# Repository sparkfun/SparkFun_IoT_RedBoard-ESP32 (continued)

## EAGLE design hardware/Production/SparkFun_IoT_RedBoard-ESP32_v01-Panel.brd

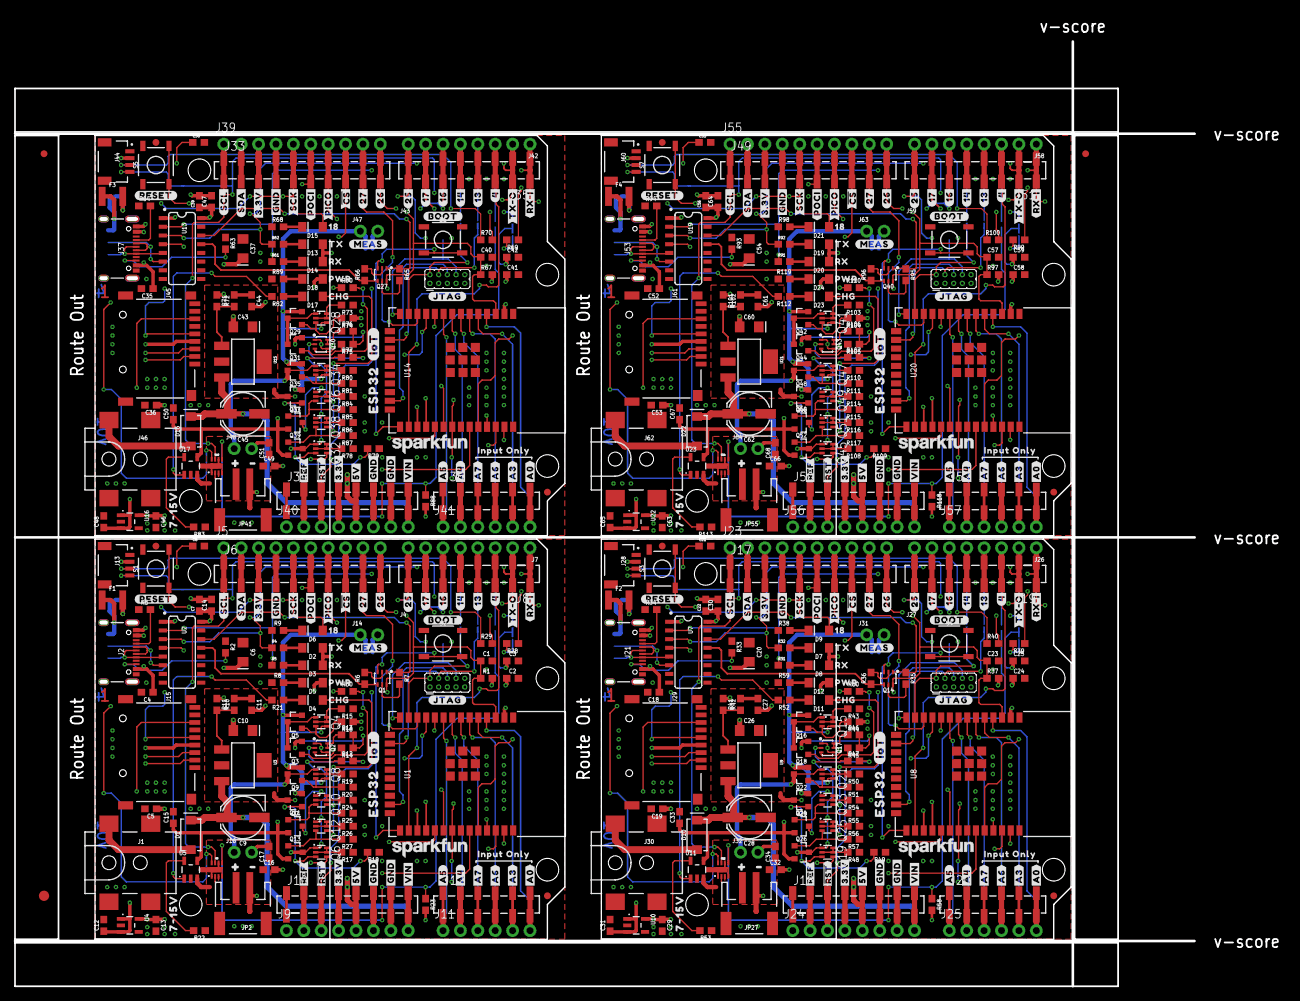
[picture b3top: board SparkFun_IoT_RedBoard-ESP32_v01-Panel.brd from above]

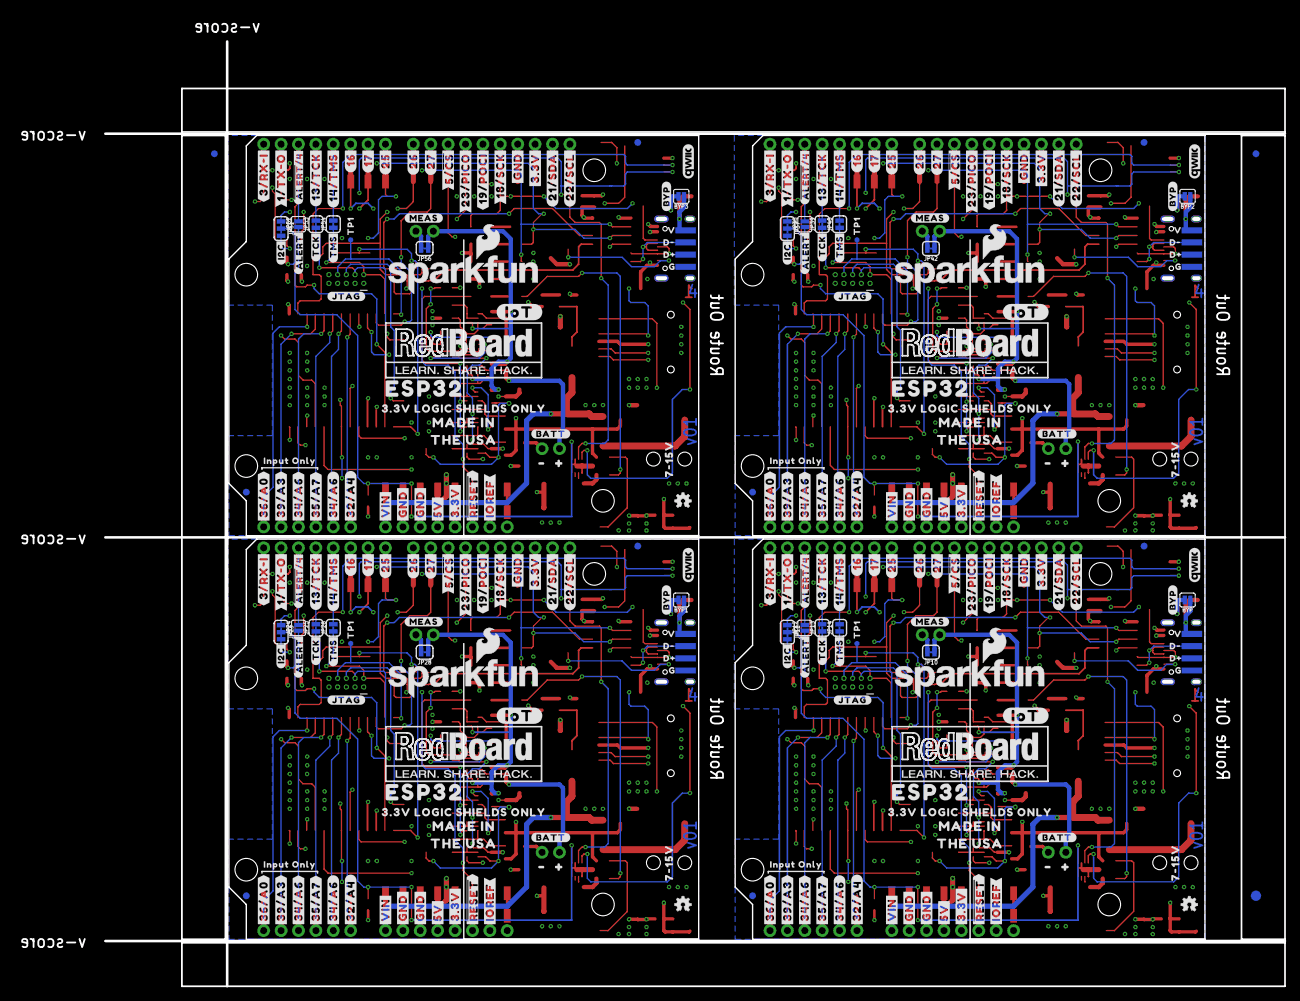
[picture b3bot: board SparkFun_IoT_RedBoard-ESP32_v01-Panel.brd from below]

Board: 4 copper layers, 172.2 x 137.9 mm, 850 parts (271 on the bottom side), 296 nets.

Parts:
BYP, BYP1, BYP2, BYP3: JUMPER-SMT_2_NO_SILK; SMT-JUMPER_2_NO_SILK
C1, C2, C4, C5, C7, C11, C12, C13, C17, C18, C19, C22, C23, C24, C27, C29, C31, C34, C35, C36, C39, C40, C41, C44, C46, C48, C51, C52, C53, C56, C57, C58, C61, C63, C65, C68: 0.1uF; 0603
C3, C14, C25, C30, C42, C47, C59, C64: 10uF; 0603
C6, C10, C20, C26, C37, C43, C54, C60: 10uF; EIA3216
C8, C21, C38, C55: 10nF; 0603
C9, C28, C45, C62: 47uF; PANASONIC_D
C15, C16, C32, C33, C49, C50, C66, C67: 4.7uF; 0603
D1, D10, D16, D22: 1A/40V/500mV; SMA-DIODE
D2, D7, D13, D19: GREEN; LED-1206-HIDDENSILK
D3, D8, D14, D20: YELLOW; LED-1206-HIDDENSILK
D4, D11, D17, D23: RED; LED-1206-HIDDENSILK
D5, D12, D18, D24: PWR; LED-1206-HIDDENSILK
D6, D9, D15, D21: BLUE; LED-1206-HIDDENSILK
E$1, E$2, E$3, E$4: FIDUCIAL-1X2
E$5, E$6: FIDUCIAL-1.5X3
F1, F2, F3, F4: 6V/2A; 1210
J1, J30, J46, J62: 5.5x2.1mm Barrel; POWER_JACK_SMD
J2, J21, J37, J53: USB C; USB-C-16P-2LAYER-PADS
J3, J22, J38, J54: USB_SOLDER_PADS; USB-SOLDER-PADS
J4, J27, J43, J59: 2X5_PTH_SILK_.05
J5, J23, J39, J55: M10NO_SILK; 1X10_NO_SILK
J6, J17, J33, J49: 1X10_SMD_COMBINED
J7, J9, J24, J26, J40, J42, J56, J58: 1X08_NO_SILK
J8, J10, J18, J19, J34, J35, J50, J51: 1X08_SMD_COMBINED
J11, J25, J41, J57: 1X06_NO_SILK
J12, J20, J36, J52: 1X06_SMD_STRAIGHT_COMBO
J13, J28, J44, J60: QWIIC_RIGHT_ANGLE; JST04_1MM_RA
J14, J16, J31, J32, J47, J48, J63, J64: 1X02_NO_SILK
J15, J29, J45, J61: MICRO-SD-PUSH-PUSH-EXT-PIN; MICROSD-EXTERNALPIN
JP1, JP7, JP8, JP9, JP19, JP20, JP21, JP22, JP33, JP34, JP35, JP36, JP47, JP48, JP49, JP50: FIDUCIAL1X2; FIDUCIAL-1X2
JP2, JP27, JP41, JP55: LiPo; JST-2-SMD
JP3, JP4, JP5, JP6, JP15, JP16, JP17, JP18, JP29, JP30, JP31, JP32, JP43, JP44, JP45, JP46: STAND-OFF
JP10, JP13, JP14, JP25, JP26, JP28, JP39, JP40, JP42, JP53, JP54, JP56: JUMPER-SMT_2_NC_TRACE_SILK; SMT-JUMPER_2_NC_TRACE_SILK
JP11, JP23, JP37, JP51: JUMPER-SMT_3_2-NC_TRACE_SILK; SMT-JUMPER_3_2-NC_TRACE_SILK
JP12, JP24, JP38, JP52: JUMPER-SMT_2_NO_SILK; SMT-JUMPER_2_NO_SILK
LOGO1, LOGO4, LOGO9, LOGO13: SFE_LOGO_NAME.1_INCH; SFE_LOGO_NAME_.1
LOGO2, LOGO5, LOGO10, LOGO14: QWIIC_LOGO_5MM; QWIIC_5MM
LOGO3, LOGO7, LOGO11, LOGO15: OSHW-LOGOMINI; OSHW-LOGO-MINI
LOGO6, LOGO8, LOGO12, LOGO16: SFE_LOGO_NAME_FLAME.2_INCH; SFE_LOGO_NAME_FLAME_.2
Q1, Q14, Q27, Q40: MBT3904DW1T1; SC70-6
Q2, Q17, Q30, Q43: SC70-6
Q3, Q5, Q7, Q9, Q11, Q13, Q16, Q18, Q20, Q22, Q24, Q26, Q29, Q31, Q33, Q35, Q37, Q39, Q42, Q44, Q46, Q48, Q50, Q52: 20V/4.2A/52mΩ/1.4W; SOT23-3
Q4, Q6, Q8, Q10, Q12, Q15, Q19, Q21, Q23, Q25, Q28, Q32, Q34, Q36, Q38, Q41, Q45, Q47, Q49, Q51: SOT363_PHILIPS
R1, R6, R7, R8, R12, R13, R14, R15, R17, R19, R23, R24, R26, R35, R36, R37, R43, R45, R46, R47, R48, R50, R54, R56, R58, R59, R65, R66, R67, R73, R75, R76, R77, R78, R80, R84, R86, R88, R89, R95, R96, R97, R103, R105, R106, R107, R108, R110, R114, R116, R118, R119: 10k; 0603
R2, R3, R33, R34, R63, R64, R93, R94: 5.1k; 0603
R4, R5, R9, R31, R32, R38, R61, R62, R68, R91, R92, R98: 4.7k; 0603
R10, R42, R72, R102: 240; 0603
R11, R41, R71, R101: 715; 0603
R16, R18, R20, R25, R27, R44, R49, R51, R55, R57, R74, R79, R81, R85, R87, R104, R109, R111, R115, R117: 47k; 0603
R21, R52, R82, R112: 1k; 0603
R22, R53, R83, R113: 2.0k; 0603
R28, R29, R39, R40, R69, R70, R99, R100: 2.2k; 0603
R30, R60, R90, R120: 100; 0603
S1, S3, S5, S7: Reset; TACTILE_SWITCH_SMD_5.2MM
S2, S4, S6, S8: GPIO0; TACTILE_SWITCH_SMD_5.2MM
TP1, TP2, TP3, TP4: TEST-POINT3; PAD.03X.03
U1, U8, U14, U20: ESP-WROOM-3232D-NARROW; ESP-WROOM-32D-NARROW
U2, U7, U13, U19: CH340C; SO016
U3, U9, U15, U21: LM1117; SOT223
U4, U10, U16, U22: 3.3V; SOT23-5
U5, U11, U17, U23: MCP73831; SOT23-5
U6, U12, U18, U24: MAX17048; DFN-8
U$1, U$87, U$201, U$301: V323252
U$2, U$3, U$202, U$302: #SCL#34
U$4, U$102, U$203, U$303: #SDA#33
U$5, U$104, U$204, U$304: #3#3V#33
U$6, U$105, U$205, U$305: #GND#32
U$7, U$106, U$206, U$306: #SCK#31
U$8, U$107, U$207, U$307: #POCI#30
U$9, U$108, U$208, U$308: #PICO#29
U$10, U$109, U$209, U$309: 1836
U$11, U$110, U$210, U$310: ##CS##28
U$12, U$111, U$211, U$311: #27#27
U$13, U$112, U$212, U$312: #26#26
U$14, U$113, U$213, U$313: TX1838
U$15, U$114, U$214, U$314: RX1839
U$16, U$115, U$215, U$315: PWR1837
U$17, U$116, U$216, U$316: CHG1840
U$18, U$117, U$217, U$317: #25#18
U$19, U$118, U$218, U$318: #17#17
U$20, U$119, U$219, U$319: #16#15
U$21, U$120, U$220, U$320: #14#14
U$22, U$121, U$221, U$321: #13#5
U$23, U$122, U$222, U$322: #4#2
U$24, U$123, U$223, U$323: #TX#O#0
U$25, U$124, U$224, U$324: #RX#I#1
U$26, U$125, U$225, U$325: #RESET#1842
U$27, U$126, U$226, U$326: #BOOT#1841
U$28, U$46, U$127, U$145, U$227, U$245, U$327, U$345: #JTAG#1847
U$29, U$128, U$228, U$328: #A0#1843
U$30, U$129, U$229, U$329: #A3#1843
U$31, U$130, U$230, U$330: #A6#1843
U$32, U$131, U$231, U$331: #A7#1843
U$33, U$132, U$232, U$332: #A4#1843
U$34, U$133, U$233, U$333: #A5#1843
U$35, U$134, U$234, U$334: #VIN#1843
U$36, U$37, U$135, U$136, U$235, U$236, U$335, U$336: #GND#1844
U$38, U$137, U$237, U$337: #5V#1845
U$39, U$138, U$238, U$338: #3#3V#1845
U$40, U$139, U$239, U$339: ##RST##1845
U$41, U$140, U$240, U$340: #REF#1846
U$42, U$81, U$141, U$178, U$241, U$278, U$341, U$378: #MEAS#1851
U$43, U$86, U$142, U$183, U$242, U$283, U$342, U$383: #1849
U$44, U$88, U$143, U$184, U$243, U$284, U$343, U$384: #1850
U$45, U$144, U$244, U$344: #BATT#1848
U$47, U$196, U$296, U$396: #IOT#132321874
U$48, U$146, U$246, U$346: ESP321855
U$49, U$101, U$147, U$199, U$247, U$299, U$347, U$399: 7#15V32321861
U$50, U$148, U$248, U$348: #39#A3#321862
U$51, U$149, U$249, U$349: #36#A0#321862
U$52, U$150, U$250, U$350: #34#A6#32321865
U$53, U$151, U$251, U$351: #35#A7#321862
U$54, U$152, U$252, U$352: #32#A4#32321865
U$55, U$153, U$253, U$353: #34#A6#321862
U$56, U$154, U$254, U$354: #VIN#321862
U$57, U$60, U$155, U$158, U$255, U$258, U$355, U$358: #GND#321863
U$58, U$156, U$256, U$356: #5V#321864
U$59, U$157, U$257, U$357: #3#3V#321864
U$61, U$159, U$259, U$359: ##RESET##321864
U$62, U$160, U$260, U$360: #IOREF#321865
U$63, U$161, U$261, U$361: #3#RX#I#32321869
U$64, U$162, U$262, U$362: #1#TX#O#32321869
U$65, U$191, U$291, U$391: ##ALERT##4#321866
U$66, U$163, U$263, U$363: #13#TCK#32321869
U$67, U$164, U$264, U$364: #14#TMS#32321869
U$68, U$165, U$265, U$365: #16#32321869
U$69, U$166, U$266, U$366: #17#32321869
U$70, U$167, U$267, U$367: #25#32321869
U$71, U$168, U$268, U$368: #26#32321869
U$72, U$169, U$269, U$369: #5##CS##32321869
U$73, U$170, U$270, U$370: #23#PICO#321866
U$74, U$171, U$271, U$371: #19#POCI#321866
U$75, U$172, U$272, U$372: #18#SCK#32321869
U$76, U$173, U$273, U$373: #21#SDA#32321869
U$77, U$174, U$274, U$374: #22#SCL#32321869
U$78, U$175, U$275, U$375: #27#32321869
U$79, U$176, U$276, U$376: #GND#321866
U$80, U$177, U$277, U$377: #3#3V#321866
U$82, U$179, U$279, U$379: #BYP#35
U$83, U$180, U$280, U$380: D#32321863
U$84, U$181, U$281, U$381: D#32321862
U$85, U$182, U$282, U$382: G32321864
U$89, U$185, U$285, U$385: #I2C#1855
U$90, U$186, U$286, U$386: ##ALERT##1852
U$91, U$187, U$287, U$387: #TMS#1854
U$92, U$188, U$288, U$388: #TCK#1853
U$93, U$195, U$295, U$395: ESP32321856
U$94, U$197, U$297, U$397: MADE_IN32321857
U$95, U$192, U$292, U$392: TP1321868
U$96, U$97, U$189, U$190, U$289, U$290, U$389, U$390: INPUT_ONLY321867
U$98, U$193, U$293, U$393: REDBOARD_LOGO
U$99, U$198, U$298, U$398: THE_USA32321858
U$100, U$194, U$294, U$394: #IOT#132321869
U$103, U$200, U$300, U$400: 3#3V_LOGIC_SHIELDS_ONLY132321876

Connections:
3.3V: C2.1, C3.1, C7.1, C13.1, C14.1, D2.A, D3.A, D5.A, J5.3, J6.3A, J6.3B, J9.2, J9.4, J10.2, J10.4, J13.2, J15.4, JP11.2, R1.2, R23.2, U1.2, U2.16, U4.5
3.3V1: C22.1, C24.1, C25.1, C29.1, C30.1, D7.A, D8.A, D12.A, J17.3A, J17.3B, J18.2, J18.4, J23.3, J24.2, J24.4, J28.2, J29.4, JP23.2, R37.2, R58.2, U7.16, U8.2, U10.5
3.3V2: C39.1, C41.1, C42.1, C46.1, C47.1, D13.A, D14.A, D18.A, J33.3A, J33.3B, J34.2, J34.4, J39.3, J40.2, J40.4, J44.2, J45.4, JP37.2, R67.2, R88.2, U13.16, U14.2, U16.5
3.3V3: C56.1, C58.1, C59.1, C63.1, C64.1, D19.A, D20.A, D24.A, J49.3A, J49.3B, J50.2, J50.4, J55.3, J56.2, J56.4, J60.2, J61.4, JP51.2, R97.2, R118.2, U19.16, U20.2, U22.5
5V: C12.1, J9.5, J10.5, J14.2, JP10.2, U4.1, U4.3
5V1: C31.1, J18.5, J24.5, J31.2, JP28.2, U10.1, U10.3
5V2: C48.1, J34.5, J40.5, J47.2, JP42.2, U16.1, U16.3
5V3: C65.1, J50.5, J56.5, J63.2, JP56.2, U22.1, U22.3
5V_CHG: C15.1, D4.A, Q10.4, Q11.2, Q12.4, Q13.2, U5.4
5V_CHG1: C33.1, D11.A, Q23.4, Q24.2, Q25.4, Q26.2, U11.4
5V_CHG2: C50.1, D17.A, Q36.4, Q37.2, Q38.4, Q39.2, U17.4
5V_CHG3: C67.1, D23.A, Q49.4, Q50.2, Q51.4, Q52.2, U23.4
5V_EXT: C10.+, C11.1, Q6.1, Q7.3, Q12.1, Q13.3, R10.2, R12.1, U3.2, U3.4
5V_EXT1: C26.+, C27.1, Q19.1, Q20.3, Q25.1, Q26.3, R42.2, R47.1, U9.2, U9.4
5V_EXT2: C43.+, C44.1, Q32.1, Q33.3, Q38.1, Q39.3, R72.2, R77.1, U15.2, U15.4
5V_EXT3: C60.+, C61.1, Q45.1, Q46.3, Q51.1, Q52.3, R102.2, R107.1, U21.2, U21.4
5V_MEAS: J14.1, JP10.1, Q4.4, Q5.2, Q6.4, Q7.2, Q8.4, Q9.2
5V_MEAS1: J31.1, JP28.1, Q15.4, Q16.2, Q19.4, Q20.2, Q21.4, Q22.2
5V_MEAS2: J47.1, JP42.1, Q28.4, Q29.2, Q32.4, Q33.2, Q34.4, Q35.2
5V_MEAS3: J63.1, JP56.1, Q41.4, Q42.2, Q45.4, Q46.2, Q47.4, Q48.2
!DTR!: Q1.4, R6.1, U2.13
!DTR!1: Q14.4, R36.1, U7.13
!DTR!2: Q27.4, R66.1, U13.13
!DTR!3: Q40.4, R96.1, U19.13
!GAUGE_ALERT!: JP12.1, R23.1, U6.5
!GAUGE_ALERT!1: JP24.1, R58.1, U12.5
!GAUGE_ALERT!2: JP38.1, R88.1, U18.5
!GAUGE_ALERT!3: JP52.1, R118.1, U24.5
!RTS!: Q1.1, R7.1, U2.14
!RTS!1: Q14.1, R35.1, U7.14
!RTS!2: Q27.1, R65.1, U13.14
!RTS!3: Q40.1, R95.1, U19.14
CC1: J2.A5, R3.2
CC2: J2.B5, R2.2
CC3: J21.B5, R33.2
CC4: J21.A5, R34.2
CC5: J37.B5, R63.2
CC6: J37.A5, R64.2
CC7: J53.B5, R93.2
CC8: J53.A5, R94.2
D+: J2.A6, J2.B6, J3.D+, U2.5
D+1: J21.A6, J21.B6, J22.D+, U7.5
D+2: J37.A6, J37.B6, J38.D+, U13.5
D+3: J53.A6, J53.B6, J54.D+, U19.5
D-: J2.A7, J2.B7, J3.D-, U2.6
D-1: J21.A7, J21.B7, J22.D-, U7.6
D-2: J37.A7, J37.B7, J38.D-, U13.6
D-3: J53.A7, J53.B7, J54.D-, U19.6
ESP32_0: Q1.3, S2.3, S2.4, U1.25
ESP32_1: Q14.3, S4.3, S4.4, U8.25
ESP32_2: Q27.3, S6.3, S6.4, U14.25
ESP32_3: Q40.3, S8.3, S8.4, U20.25
ESP32_ADC0: J11.6, J12.6, U1.4
ESP32_ADC1: J20.6, J25.6, U8.4
ESP32_ADC2: J20.5, J25.5, U8.5
ESP32_ADC3: J11.5, J12.5, U1.5
ESP32_ADC4: J11.2, J12.2, U1.8
ESP32_ADC5: J11.1, J12.1, U1.9
ESP32_ADC6: J11.4, J12.4, U1.6
ESP32_ADC7: J11.3, J12.3, U1.7
ESP32_ADC8: J20.4, J25.4, U8.6
ESP32_ADC9: J20.3, J25.3, U8.7
ESP32_ADC10: J20.1, J25.1, U8.9
ESP32_ADC11: J20.2, J25.2, U8.8
ESP32_ADC12: J36.6, J41.6, U14.4
ESP32_ADC13: J36.5, J41.5, U14.5
ESP32_ADC14: J36.4, J41.4, U14.6
ESP32_ADC15: J36.3, J41.3, U14.7
ESP32_ADC16: J36.1, J41.1, U14.9
ESP32_ADC17: J36.2, J41.2, U14.8
ESP32_ADC18: J52.6, J57.6, U20.4
ESP32_ADC19: J52.5, J57.5, U20.5
ESP32_ADC20: J52.4, J57.4, U20.6
ESP32_ADC21: J52.3, J57.3, U20.7
ESP32_ADC22: J52.1, J57.1, U20.9
ESP32_ADC23: J52.2, J57.2, U20.8
ESP32_EN: C1.1, J9.3, J10.3, Q1.6, R1.1, S1.3, S1.4, U1.3
ESP32_EN1: C23.1, J18.3, J24.3, Q14.6, R37.1, S3.3, S3.4, U8.3
ESP32_EN2: C40.1, J34.3, J40.3, Q27.6, R67.1, S5.3, S5.4, U14.3
ESP32_EN3: C57.1, J50.3, J56.3, Q40.6, R97.1, S7.3, S7.4, U20.3
ESP32_GPIO3: J19.3, J26.3, JP24.2, U8.26
ESP32_GPIO4: J7.3, J8.3, JP12.2, U1.26
ESP32_GPIO5: J19.7, J26.7, U8.28
ESP32_GPIO5_!CS!: J5.8, J6.8A, J6.8B, J15.2, U1.29
ESP32_GPIO5_!CS!1: J17.8A, J17.8B, J23.8, J29.2, U8.29
ESP32_GPIO5_!CS!2: J33.8A, J33.8B, J39.8, J45.2, U14.29
ESP32_GPIO5_!CS!3: J49.8A, J49.8B, J55.8, J61.2, U20.29
ESP32_GPIO6: J19.8, J26.8, U8.10
ESP32_GPIO7: J17.10A, J17.10B, J23.10, U8.11
ESP32_GPIO8: J17.9A, J17.9B, J23.9, U8.12
ESP32_GPIO9: J19.6, J26.6, U8.27
ESP32_GPIO11: J35.3, J42.3, JP38.2, U14.26
ESP32_GPIO12: J35.7, J42.7, U14.28
ESP32_GPIO12_TDI: J4.8, TP1.1, U1.14
ESP32_GPIO12_TDI1: J27.8, TP2.1, U8.14
ESP32_GPIO12_TDI2: J43.8, TP3.1, U14.14
ESP32_GPIO12_TDI3: J59.8, TP4.1, U20.14
ESP32_GPIO13: J35.8, J42.8, U14.10
ESP32_GPIO13_HDR: J7.4, J8.4, JP13.2
ESP32_GPIO13_HDR1: J19.4, J26.4, JP25.2
ESP32_GPIO13_HDR2: J35.4, J42.4, JP39.2
ESP32_GPIO13_HDR3: J51.4, J58.4, JP53.2
ESP32_GPIO13_TCK: J4.4, JP13.1, U1.16
ESP32_GPIO13_TCK1: J27.4, JP25.1, U8.16
ESP32_GPIO13_TCK2: J43.4, JP39.1, U14.16
ESP32_GPIO13_TCK3: J59.4, JP53.1, U20.16
ESP32_GPIO14: J33.10A, J33.10B, J39.10, U14.11
ESP32_GPIO14_HDR: J7.5, J8.5, JP14.2
ESP32_GPIO14_HDR1: J19.5, J26.5, JP26.2
ESP32_GPIO14_HDR2: J35.5, J42.5, JP40.2
ESP32_GPIO14_HDR3: J51.5, J58.5, JP54.2
ESP32_GPIO14_TMS: J4.2, JP14.1, U1.13
ESP32_GPIO14_TMS1: J27.2, JP26.1, U8.13
ESP32_GPIO14_TMS2: J43.2, JP40.1, U14.13
ESP32_GPIO14_TMS3: J59.2, JP54.1, U20.13
ESP32_GPIO15: J33.9A, J33.9B, J39.9, U14.12
ESP32_GPIO15_TDO: J4.6, U1.23
ESP32_GPIO15_TDO1: J27.6, U8.23
ESP32_GPIO15_TDO2: J43.6, U14.23
ESP32_GPIO15_TDO3: J59.6, U20.23
ESP32_GPIO16: J7.6, J8.6, U1.27
ESP32_GPIO17: J7.7, J8.7, U1.28
ESP32_GPIO18: J35.6, J42.6, U14.27
ESP32_GPIO18_SCK: D6.A, J5.5, J6.5A, J6.5B, J15.5, U1.30
ESP32_GPIO18_SCK1: D9.A, J17.5A, J17.5B, J23.5, J29.5, U8.30
ESP32_GPIO18_SCK2: D15.A, J33.5A, J33.5B, J39.5, J45.5, U14.30
ESP32_GPIO18_SCK3: D21.A, J49.5A, J49.5B, J55.5, J61.5, U20.30
ESP32_GPIO19_POCI: J5.6, J6.6A, J6.6B, J15.7, U1.31
ESP32_GPIO19_POCI1: J17.6A, J17.6B, J23.6, J29.7, U8.31
ESP32_GPIO19_POCI2: J33.6A, J33.6B, J39.6, J45.7, U14.31
ESP32_GPIO19_POCI3: J49.6A, J49.6B, J55.6, J61.7, U20.31
ESP32_GPIO20: J51.3, J58.3, JP52.2, U20.26
ESP32_GPIO21: J51.7, J58.7, U20.28
ESP32_GPIO22: J51.8, J58.8, U20.10
ESP32_GPIO23: J49.10A, J49.10B, J55.10, U20.11
ESP32_GPIO23_PICO: J5.7, J6.7A, J6.7B, J15.3, U1.37
ESP32_GPIO23_PICO1: J17.7A, J17.7B, J23.7, J29.3, U8.37
ESP32_GPIO23_PICO2: J33.7A, J33.7B, J39.7, J45.3, U14.37
ESP32_GPIO23_PICO3: J49.7A, J49.7B, J55.7, J61.3, U20.37
ESP32_GPIO24: J49.9A, J49.9B, J55.9, U20.12
ESP32_GPIO25: J7.8, J8.8, U1.10
ESP32_GPIO26: J5.10, J6.10A, J6.10B, U1.11
ESP32_GPIO27: J5.9, J6.9A, J6.9B, U1.12
ESP32_GPIO28: J51.6, J58.6, U20.27
ESP32_RXD0: J7.1, J8.1, R5.1, U1.34, U2.2
ESP32_RXD1: J19.1, J26.1, R31.1, U7.2, U8.34
ESP32_RXD2: J35.1, J42.1, R61.1, U13.2, U14.34
ESP32_RXD3: J51.1, J58.1, R91.1, U19.2, U20.34
ESP32_SCL: J5.1, J6.1A, J6.1B, J13.4, R28.1, U1.36, U6.7
ESP32_SCL1: J17.1A, J17.1B, J23.1, J28.4, R39.1, U8.36, U12.7
ESP32_SCL2: J33.1A, J33.1B, J39.1, J44.4, R69.1, U14.36, U18.7
ESP32_SCL3: J49.1A, J49.1B, J55.1, J60.4, R99.1, U20.36, U24.7
ESP32_SDA: J5.2, J6.2A, J6.2B, J13.3, R29.1, U1.33, U6.8
ESP32_SDA1: J17.2A, J17.2B, J23.2, J28.3, R40.1, U8.33, U12.8
ESP32_SDA2: J33.2A, J33.2B, J39.2, J44.3, R70.1, U14.33, U18.8
ESP32_SDA3: J49.2A, J49.2B, J55.2, J60.3, R100.1, U20.33, U24.8
ESP32_TXD0: J7.2, J8.2, R4.1, U1.35, U2.3
ESP32_TXD1: J19.2, J26.2, R32.1, U7.3, U8.35
ESP32_TXD2: J35.2, J42.2, R62.1, U13.3, U14.35
ESP32_TXD3: J51.2, J58.2, R92.1, U19.3, U20.35
GND: C1.2, C2.2, C3.2, C4.2, C5.2, C6.-, C7.2, C8.2, C9.-, C10.-, C11.2, C12.2, C13.2, C14.2, C15.2, C16.2, C17.2, J1.GND, J2.GND, J2.GND2, J3.GND, J4.3, J4.5, J4.7, J4.9, J5.4, J6.4A, J6.4B, J9.6, J9.7, J10.6, J10.7, J13.1, J15.6, J15.10, J15.11, J15.12, J15.13, J16.2, JP2.1, Q2.1, Q2.4, R2.1, R3.1, R8.1, R9.1, R11.1, R15.1, R16.1, R17.1, R18.1, R19.1, R20.1, R22.1, R24.1, R25.1, R26.1, R27.1, S1.1, S1.2, S2.1, S2.2, U1.1, U1.15, U1.38, U1.GND1, U1.GNDT1, U1.GNDT2, U1.GNDT3, U1.GNDT4, U1.GNDT5, U1.GNDT6, U1.GNDT7, U1.GNDT8, U2.1, U4.2, U5.2, U6.1, U6.4, U6.6, U6.9
GND2: C18.2, C19.2, C20.-, C21.2, C22.2, C23.2, C24.2, C25.2, C26.-, C27.2, C28.-, C29.2, C30.2, C31.2, C32.2, C33.2, C34.2, J17.4A, J17.4B, J18.6, J18.7, J21.GND, J21.GND2, J22.GND, J23.4, J24.6, J24.7, J27.3, J27.5, J27.7, J27.9, J28.1, J29.6, J29.10, J29.11, J29.12, J29.13, J30.GND, J32.2, JP27.1, Q17.1, Q17.4, R33.1, R34.1, R38.1, R41.1, R43.1, R44.1, R48.1, R49.1, R50.1, R51.1, R53.1, R54.1, R55.1, R56.1, R57.1, R59.1, S3.1, S3.2, S4.1, S4.2, U7.1, U8.1, U8.15, U8.38, U8.GND1, U8.GNDT1, U8.GNDT2, U8.GNDT3, U8.GNDT4, U8.GNDT5, U8.GNDT6, U8.GNDT7, U8.GNDT8, U10.2, U11.2, U12.1, U12.4, U12.6, U12.9
GND4: C35.2, C36.2, C37.-, C38.2, C39.2, C40.2, C41.2, C42.2, C43.-, C44.2, C45.-, C46.2, C47.2, C48.2, C49.2, C50.2, C51.2, J33.4A, J33.4B, J34.6, J34.7, J37.GND, J37.GND2, J38.GND, J39.4, J40.6, J40.7, J43.3, J43.5, J43.7, J43.9, J44.1, J45.6, J45.10, J45.11, J45.12, J45.13, J46.GND, J48.2, JP41.1, Q30.1, Q30.4, R63.1, R64.1, R68.1, R71.1, R73.1, R74.1, R78.1, R79.1, R80.1, R81.1, R83.1, R84.1, R85.1, R86.1, R87.1, R89.1, S5.1, S5.2, S6.1, S6.2, U13.1, U14.1, U14.15, U14.38, U14.GND1, U14.GNDT1, U14.GNDT2, U14.GNDT3, U14.GNDT4, U14.GNDT5, U14.GNDT6, U14.GNDT7, U14.GNDT8, U16.2, U17.2, U18.1, U18.4, U18.6, U18.9
GND6: C52.2, C53.2, C54.-, C55.2, C56.2, C57.2, C58.2, C59.2, C60.-, C61.2, C62.-, C63.2, C64.2, C65.2, C66.2, C67.2, C68.2, J49.4A, J49.4B, J50.6, J50.7, J53.GND, J53.GND2, J54.GND, J55.4, J56.6, J56.7, J59.3, J59.5, J59.7, J59.9, J60.1, J61.6, J61.10, J61.11, J61.12, J61.13, J62.GND, J64.2, JP55.1, Q43.1, Q43.4, R93.1, R94.1, R98.1, R101.1, R103.1, R104.1, R108.1, R109.1, R110.1, R111.1, R113.1, R114.1, R115.1, R116.1, R117.1, R119.1, S7.1, S7.2, S8.1, S8.2, U19.1, U20.1, U20.15, U20.38, U20.GND1, U20.GNDT1, U20.GNDT2, U20.GNDT3, U20.GNDT4, U20.GNDT5, U20.GNDT6, U20.GNDT7, U20.GNDT8, U22.2, U23.2, U24.1, U24.4, U24.6, U24.9
unnamed: R21.2, U5.1
unnamed: D5.C, R8.2
unnamed: D6.C, R9.2
unnamed: D4.C, R21.1
unnamed: D2.C, R4.2
unnamed: C8.1, U2.4
unnamed: D3.C, R5.2
unnamed: Q6.2, Q6.5, Q6.6, R17.2
unnamed: Q3.1, R14.2, R30.2
unnamed: Q6.3, Q7.1, R18.2
unnamed: Q2.3, R30.1
unnamed: Q4.2, Q4.5, Q4.6, R15.2
unnamed: Q8.2, Q8.5, Q8.6, R19.2
unnamed: R22.2, U5.5
unnamed: R10.1, R11.2, U3.1
unnamed: Q4.3, Q5.1, R16.2
unnamed: Q8.3, Q9.1, R20.2
unnamed: JP11.3, R28.2
unnamed: C21.1, U7.4
unnamed: JP11.1, R29.2
unnamed: Q2.2, R12.2
unnamed: Q2.5, Q2.6, R13.1
unnamed: Q10.3, Q11.1, R25.2
unnamed: Q1.5, R7.2
unnamed: Q1.2, R6.2
unnamed: Q10.2, Q10.5, Q10.6, R24.2
unnamed: Q14.5, R35.2
unnamed: Q12.3, Q13.1, R27.2
unnamed: Q12.2, Q12.5, Q12.6, R26.2
unnamed: Q14.2, R36.2
unnamed: D7.C, R32.2
unnamed: D8.C, R31.2
unnamed: JP23.3, R39.2
unnamed: JP23.1, R40.2
unnamed: R41.2, R42.1, U9.1
unnamed: Q15.2, Q15.5, Q15.6, R43.2
unnamed: Q15.3, Q16.1, R44.2
unnamed: Q17.2, R47.2
unnamed: Q17.5, Q17.6, R46.1
unnamed: Q19.3, Q20.1, R49.2
unnamed: Q19.2, Q19.5, Q19.6, R48.2
unnamed: Q21.2, Q21.5, Q21.6, R50.2
unnamed: Q21.3, Q22.1, R51.2
unnamed: R53.2, U11.5
unnamed: R52.2, U11.1
unnamed: D11.C, R52.1
unnamed: Q23.3, Q24.1, R55.2
unnamed: Q23.2, Q23.5, Q23.6, R54.2
unnamed: Q25.3, Q26.1, R57.2
unnamed: Q25.2, Q25.5, Q25.6, R56.2
unnamed: D12.C, R59.2
unnamed: D9.C, R38.2
unnamed: Q18.1, R45.2, R60.2
unnamed: Q17.3, R60.1
unnamed: C38.1, U13.4
unnamed: Q27.5, R65.2
unnamed: Q27.2, R66.2
unnamed: D13.C, R62.2
unnamed: D14.C, R61.2
unnamed: JP37.3, R69.2
unnamed: JP37.1, R70.2
unnamed: R71.2, R72.1, U15.1
unnamed: Q28.2, Q28.5, Q28.6, R73.2
unnamed: Q28.3, Q29.1, R74.2
unnamed: Q30.2, R77.2
unnamed: Q30.5, Q30.6, R76.1
unnamed: Q32.3, Q33.1, R79.2
unnamed: Q32.2, Q32.5, Q32.6, R78.2
unnamed: Q34.2, Q34.5, Q34.6, R80.2
unnamed: Q34.3, Q35.1, R81.2
unnamed: R83.2, U17.5
unnamed: R82.2, U17.1
unnamed: D17.C, R82.1
unnamed: Q36.3, Q37.1, R85.2
unnamed: Q36.2, Q36.5, Q36.6, R84.2
unnamed: Q38.3, Q39.1, R87.2
unnamed: Q38.2, Q38.5, Q38.6, R86.2
unnamed: D18.C, R89.2
unnamed: D15.C, R68.2
unnamed: Q31.1, R75.2, R90.2
unnamed: Q30.3, R90.1
unnamed: C55.1, U19.4
unnamed: Q40.5, R95.2
unnamed: Q40.2, R96.2
unnamed: D19.C, R92.2
unnamed: D20.C, R91.2
unnamed: JP51.3, R99.2
unnamed: JP51.1, R100.2
unnamed: R101.2, R102.1, U21.1
unnamed: Q41.2, Q41.5, Q41.6, R103.2
unnamed: Q41.3, Q42.1, R104.2
unnamed: Q43.2, R107.2
unnamed: Q43.5, Q43.6, R106.1
unnamed: Q45.3, Q46.1, R109.2
unnamed: Q45.2, Q45.5, Q45.6, R108.2
unnamed: Q47.2, Q47.5, Q47.6, R110.2
unnamed: Q47.3, Q48.1, R111.2
unnamed: R113.2, U23.5
unnamed: R112.2, U23.1
unnamed: D23.C, R112.1
unnamed: Q49.3, Q50.1, R115.2
unnamed: Q49.2, Q49.5, Q49.6, R114.2
unnamed: Q51.3, Q52.1, R117.2
unnamed: Q51.2, Q51.5, Q51.6, R116.2
unnamed: D24.C, R119.2
unnamed: D21.C, R98.2
unnamed: Q44.1, R105.2, R120.2
unnamed: Q43.3, R120.1
PWRIN: D1.A, J1.VIN0
PWRIN1: D10.A, J30.VIN0
PWRIN2: D16.A, J46.VIN0
PWRIN3: D22.A, J62.VIN0
VBUS: BYP.1, C4.1, F1.1, J2.VBUS1, J2.VBUS2, J3.VBUS
VBUS1: BYP1.1, C18.1, F2.1, J21.VBUS1, J21.VBUS2, J22.VBUS
VBUS2: BYP2.1, C35.1, F3.1, J37.VBUS1, J37.VBUS2, J38.VBUS
VBUS3: BYP3.1, C52.1, F4.1, J53.VBUS1, J53.VBUS2, J54.VBUS
VIN: C9.+, D1.C, J9.8, J10.8, U3.3
VIN1: C28.+, D10.C, J18.8, J24.8, U9.3
VIN2: C45.+, D16.C, J34.8, J40.8, U15.3
VIN3: C62.+, D22.C, J50.8, J56.8, U21.3
VUSB_PROT: Q3.3, Q4.1, Q5.3
VUSB_PROT1: Q15.1, Q16.3, Q18.3
VUSB_PROT2: Q28.1, Q29.3, Q31.3
VUSB_PROT3: Q41.1, Q42.3, Q44.3
V_BATT: C16.1, C17.1, J16.1, JP2.2, Q8.1, Q9.3, U5.3, U6.2, U6.3
V_BATT1: C32.1, C34.1, J32.1, JP27.2, Q21.1, Q22.3, U11.3, U12.2, U12.3
V_BATT2: C49.1, C51.1, J48.1, JP41.2, Q34.1, Q35.3, U17.3, U18.2, U18.3
V_BATT3: C66.1, C68.1, J64.1, JP55.2, Q47.1, Q48.3, U23.3, U24.2, U24.3
V_USB: BYP.2, C5.1, C6.+, F1.2, Q3.2, Q10.1, Q11.3, R13.2, R14.1
V_USB1: BYP1.2, C19.1, C20.+, F2.2, Q18.2, Q23.1, Q24.3, R45.1, R46.2
V_USB2: BYP2.2, C36.1, C37.+, F3.2, Q31.2, Q36.1, Q37.3, R75.1, R76.2
V_USB3: BYP3.2, C53.1, C54.+, F4.2, Q44.2, Q49.1, Q50.3, R105.1, R106.2

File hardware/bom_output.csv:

Qty, PROD_ID, Names, Value, Package
9, CAP-00810, C1; C2; C4; C5; C7; C11; C12; C13; C17, 0.1uF, 0603
2, CAP-11015, C3; C14, 10uF, 0603
2, CAP-00811, C6; C10, 10uF, EIA3216
1, CAP-00867, C8, 10nF, 0603
1, CAP-08478, C9, 47uF, PANASONIC_D
2, CAP-14106, C15; C16, 4.7uF, 0603
1, DIO-08053, D1, 1A/40V/500mV, SMA-DIODE
1, DIO-00862, D2, GREEN, LED-1206-HIDDENSILK
1, DIO-09909, D3, YELLOW, LED-1206-HIDDENSILK
1, DIO-09912, D4, RED, LED-1206-HIDDENSILK
1, DIO-00862, D5, PWR, LED-1206-HIDDENSILK
1, DIO-09911, D6, BLUE, LED-1206-HIDDENSILK
1, RES-14313, F1, 6V/2A, 1210
1, CONN-08106, J1, 5.5x2.1mm Barrel, POWER_JACK_SMD
1, CONN-14122, J2, USB C, USB-C-16P-2LAYER-PADS
1, CONN-11219, J5, M10NO_SILK, 1X10_NO_SILK
1, CONN-11219, J6, , 1X10_SMD_COMBINED
2, CONN-08438, J7; J9, , 1X08_NO_SILK
2, CONN-10204, J8; J10, , 1X08_SMD_COMBINED
1, CONN-08437, J11, , 1X06_NO_SILK
1, CONN-10203, J12, , 1X06_SMD_STRAIGHT_COMBO
1, CONN-13694, J13, QWIIC_RIGHT_ANGLE, JST04_1MM_RA
1, CONN-16110, J15, MICRO-SD-PUSH-PUSH-EXT-PIN, MICROSD-EXTERNALPIN
1, CONN-11443, JP2, LiPo, JST-2-SMD
1, TRANS-13337, Q1, MBT3904DW1T1, SC70-6
1, TRANS-13337, Q2, , SC70-6
6, TRANS-14388, Q3; Q5; Q7; Q9; Q11; Q13, 20V/4.2A/52mΩ/1.4W, SOT23-3
5, TRANS-14386, Q4; Q6; Q8; Q10; Q12, , SOT363_PHILIPS
13, RES-00824, R1; R6; R7; R8; R12; R13; R14; R15; R17; R19; R23; R24; R26, 10k, 0603
2, RES-12083, R2; R3, 5.1k, 0603
3, RES-07857, R4; R5; R9, 4.7k, 0603
1, RES-07849, R10, 240, 0603
1, RES-07850, R11, 715, 0603
5, RES-07871, R16; R18; R20; R25; R27, 47k, 0603
1, RES-07856, R21, 1k, 0603
1, RES-08296, R22, 2.0k, 0603
2, RES-08272, R28; R29, 2.2k, 0603
1, RES-07863, R30, 100, 0603
1, SWCH-14139, S1, Reset, TACTILE_SWITCH_SMD_5.2MM
1, SWCH-14139, S2, GPIO0, TACTILE_SWITCH_SMD_5.2MM
1, IC-15676, U1, ESP-WROOM-3232D-NARROW, ESP-WROOM-32D-NARROW
1, IC-14038, U2, CH340C, SO016
1, VREG-08170, U3, LM1117, SOT223
1, VREG-12457, U4, 3.3V, SOT23-5
1, IC-09995, U5, MCP73831, SOT23-5
1, IC-12551, U6, MAX17048, DFN-8
